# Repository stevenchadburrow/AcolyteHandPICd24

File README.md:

<b>Acolyte Hand PIC'd 24</b>

This is a single-chip retro-style computer using only the PIC24EP512GP204 microcontroller.  Inspired by Voja Antonic's design found here:  http://www.voja.rs/PROJECTS/GAME_HTM/1_intro.htm

It is designed to output VGA display at 320x240 with 16 colors, and 2-voice audio square waves.

It is designed to receive input from a Sega Genesis controller, PS/2 Keyboard or Mouse, and 8 on-board buttons.

It is designed to use a MicroSD Card Adapter, and an FT232RL USB Adapter.

Programmed using MPLAB IDE X via a PICkit3.

See my Youtube video for the Bad Apple demo. Either <a href="https://www.youtube.com/watch?v=rc4UsAqcSHg">without audio</a> or <a href="https://youtu.be/sSq6TWw3NXU">with audio</a>.

Also see my 'Pokemon Clone', video link <a href="https://youtu.be/8EHRpKk9gPc">here</a>.  Although I am using the Tuxemon game art assets, this project is not the Tuxemon game, nor are the creators of the Tuxemon game in charge of this project.  This project was simply inspired by the Tuxemon game.

Needed Changes:

*** LED silkscreen is confusing!!! ***

*** ICSP pins physically block the SDcard and FT232RL adapters!!! ***

*** Connected an MCP2221 to the USB connector for serial data transfer!!! ***

*** Tested with LCD, speaker, and with additional PIC24 chip for USB capability!!! ***

Updates:

Been working with the PIC24FJ128GB202 for USB capability.  Using the MLA projects from Microchip, I was able to combine USB Host capabilities for using Keyboad, Mouse, and Mass Storage Device.  See my .ZIP file for the entire project and all associated code.  It is connected to this main board through an RX/TX UART pair, currently at 9600 baud.  

A full 16-colors are available!

Tetra always seems to be the first game for any system.

It can even run Bad Apple!

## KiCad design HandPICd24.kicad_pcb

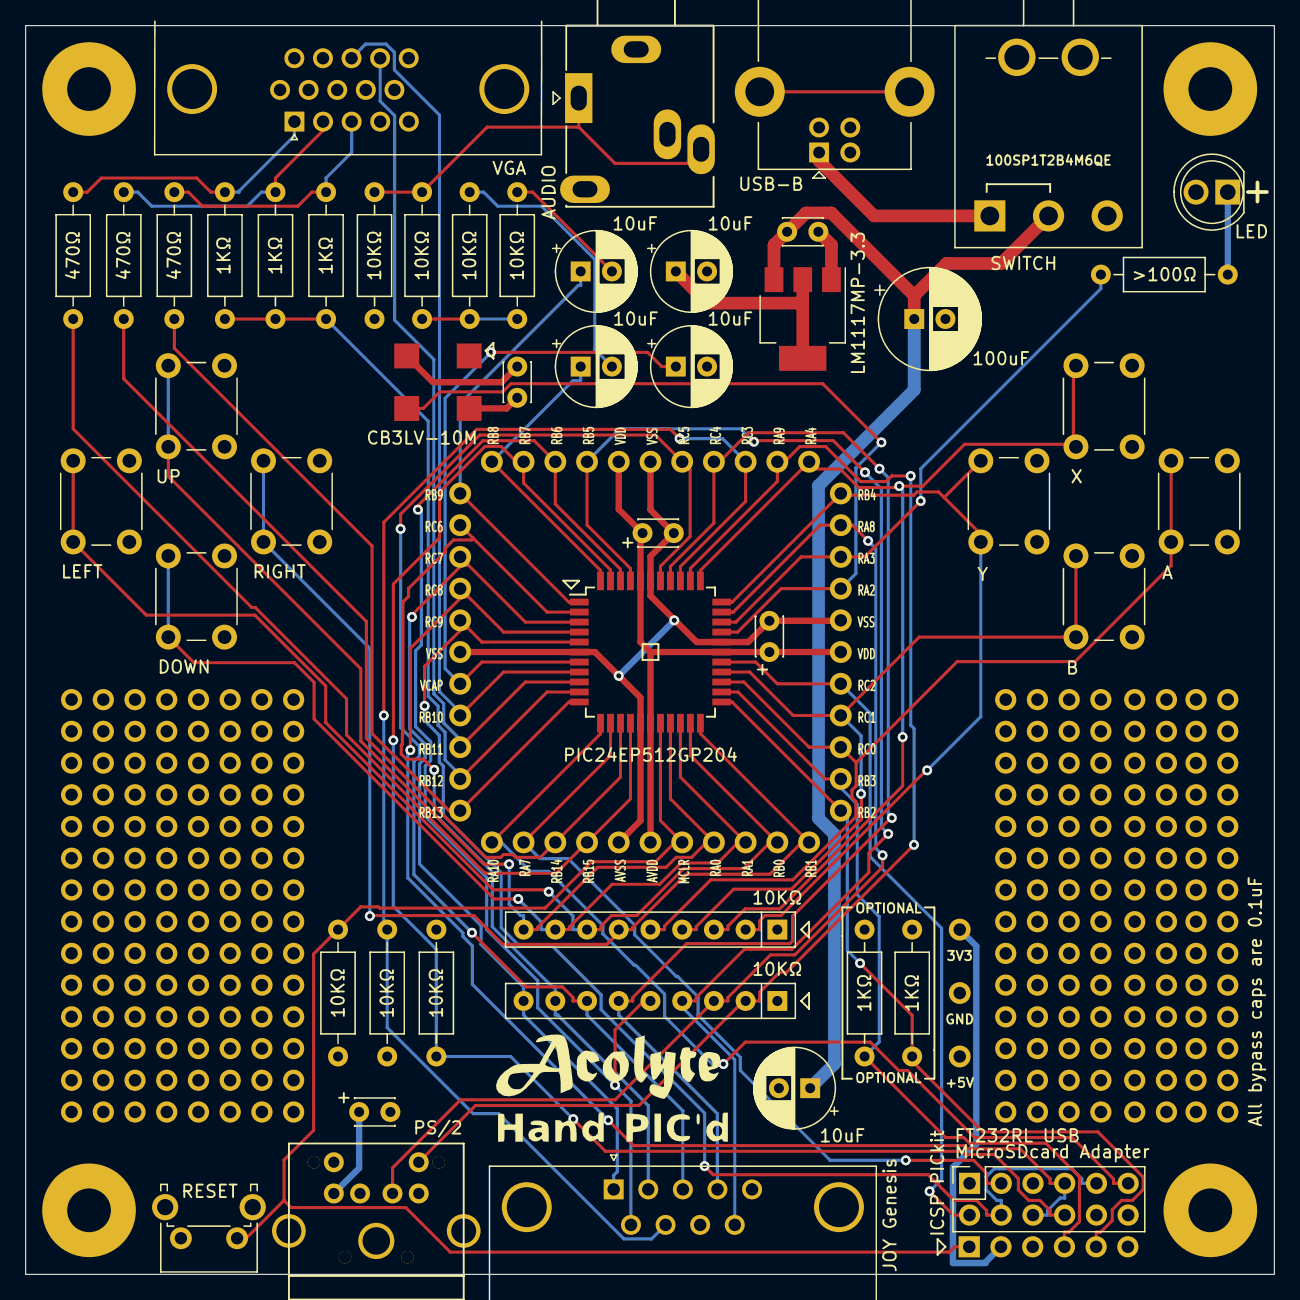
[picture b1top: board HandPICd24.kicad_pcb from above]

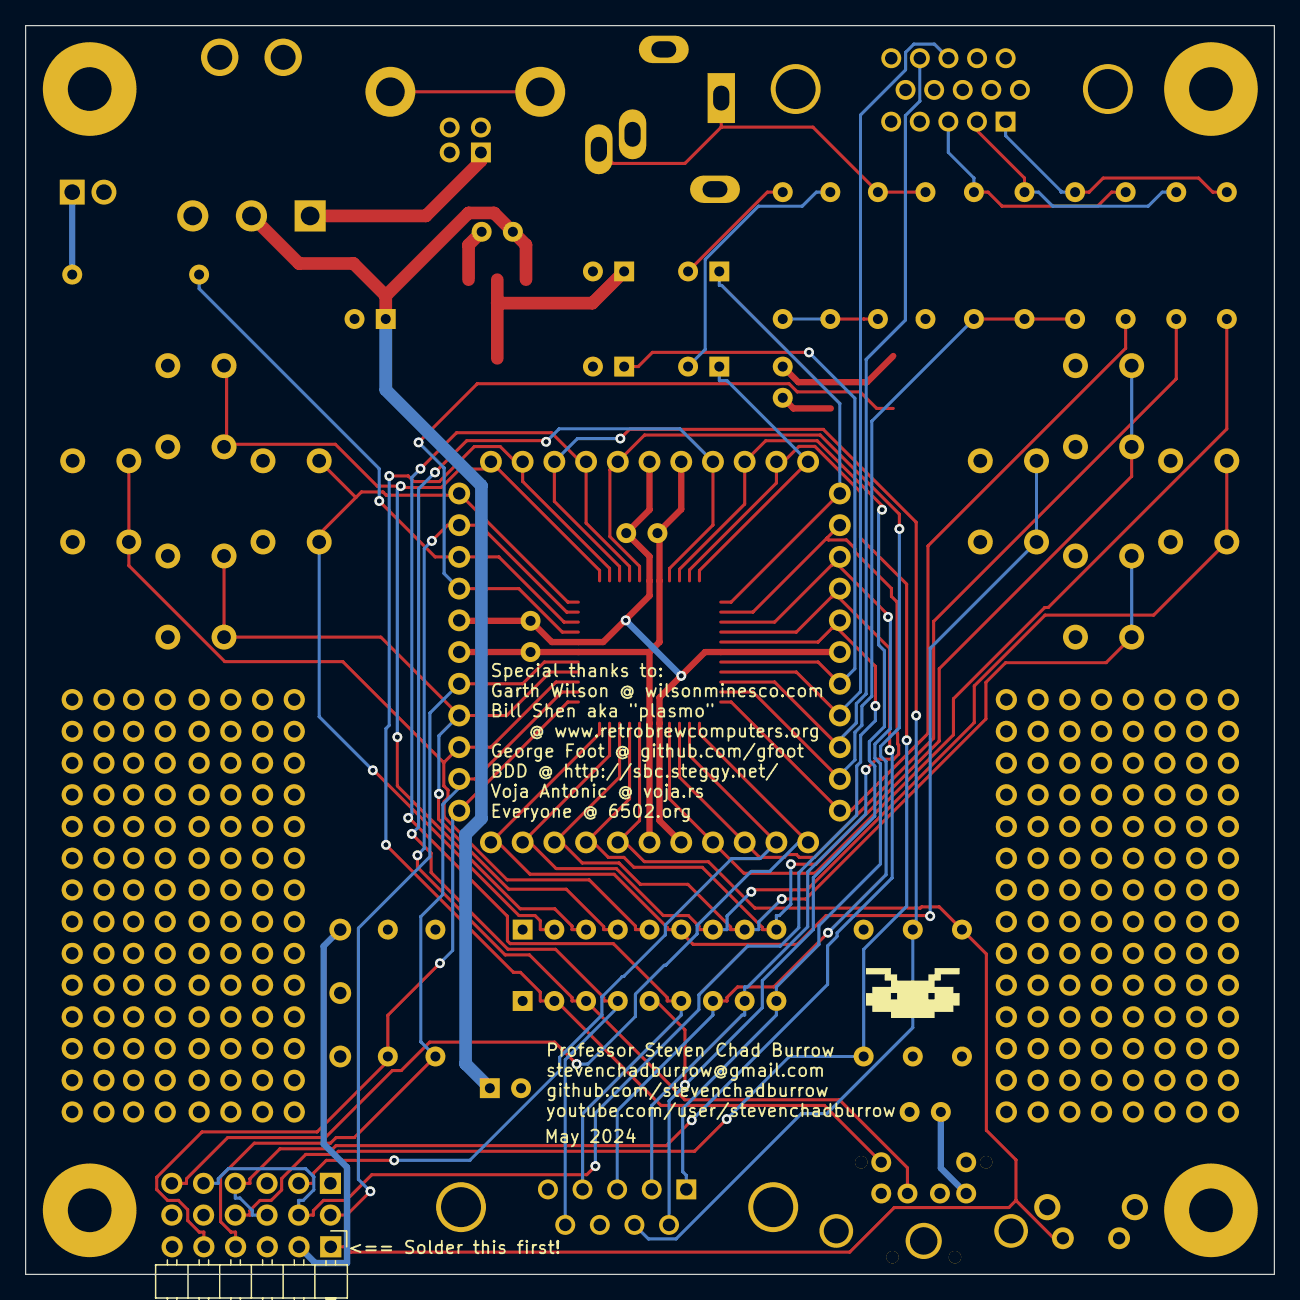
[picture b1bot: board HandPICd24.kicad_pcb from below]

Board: 4 copper layers, 100.0 x 100.0 mm, 112 parts (2 on the bottom side), 49 nets.

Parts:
C1, C3, C4, C6, C8: C_Polarized_Small_US; CP_Radial_D6.3mm_P2.50mm
C2: C_Polarized_US; CP_Radial_D8.0mm_P2.50mm
C5, C7, C19, C25, C28: C_Small; C_Disc_D3.0mm_W2.0mm_P2.50mm
D1: LED; CustomLED
G101: LOGO; AcolyteTitle
G102: LOGO; HandPickedTitle
G103: LOGO; Mystery
J1: Conn_02x06_Odd_Even; PinSocket_2x06_P2.54mm_Vertical
J2: Mini-DIN-6; PS2_Din6
J3: DE9_Plug; DSUB-9_Male_Horizontal_P2.77x2.84mm_EdgePinOffset7.70mm_Hou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
J4: USB_B; USB_B_Lumberg_2411_02_Horizontal
J5: DE15_Receptacle_HighDensity; DSUB-15-HD_Female_Horizontal_P2.29x2.54mm_VGA
J6: AudioJack3; BIGJack_3.5mm_Ledino_KB3SPRS_Horizontal
J10, J11, J12, J13, J14, J15, J16, J17: Conn_02x14_Odd_Even; BLANK-PinHeader_2x14_P2.54mm_Vertical
J18: Conn_01x06; PinHeader_1x06_P2.54mm_Horizontal
R1, R2, R3, R4, R5, R6, R7, R8, R9, R10, R11, R12, R13, R14, R15, R17: R_US; R_Axial_DIN0207_L6.3mm_D2.5mm_P10.16mm_Horizontal
RN1, RN2: R_Network08_US; R_Array_SIP9
SW1: SW_Push; SW_Tactile_SPST_Angled_PTS645Vx83-2LFS
SW2, SW4, SW5, SW6, SW7, SW8, SW9, SW10: SW_Push; SW_PUSH_6mm_H5mm
SW3: SW_SPDT; SPDT-100SP1T2B4M6QE
TP1, TP2, TP3, TP4: TestPoint; ScrewHole-4-40
TP5, TP6, TP7, TP8, TP9, TP10, TP11, TP12, TP13, TP14, TP15, TP16, TP17, TP18, TP19, TP20, TP21, TP22, TP23, TP24, TP25, TP26, TP27, TP28, TP29, TP30, TP31, TP32, TP33, TP34, TP35, TP36, TP37, TP38, TP39, TP40, TP41, TP42, TP43, TP44, TP45, TP46, TP47, TP48, TP49, TP50, TP53: TestPoint; TestPointStdTHT
U1: PIC24EP512GP204; TQFP-44_10x10mm_P0.8mm
U2: LM1117MP-3.3; SOT-223-3_TabPin2
X1: CB3LV; Oscillator_SMD_EuroQuartz_XO91-4Pin_7.0x5.0mm

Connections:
+3V3: C6.1, C19.2, C25.2, C28.2, D1.2 (A), J18.2, R4.2, R7.2, R15.2, RN2.1 (common), TP21.1, TP32.1, TP44.1, TP53.1, U1.17 (AVDD), U1.28 (VDD), U1.40 (VDD), U2.2 (VO), X1.4 (V+)
+5V: C2.1, C5.2, C7.2, C8.1, J1.10, J2.4, J3.5, R1.2, R17.2, RN1.1 (common), SW3.2 (B), TP50.1, U2.3 (VI)
AUDIO-COMBINED: R3.2, R5.1, R6.1
AUDIO-NEG-A: C4.2, R6.2
AUDIO-NEG-B: C3.2, R5.2
AUDIO-OUT: J6.R, J6.T, R2.2, R3.1
AUDIO-SOURCE-A: C4.1, TP5.1, U1.1 (RB9/RP41*+)
AUDIO-SOURCE-B: C3.1, TP48.1, U1.44 (RB8/RP40+)
BLUE: J5.3, R10.2, R13.2
BUTTON-A: RN2.5 (R4), SW7.1, TP29.1, U1.25 (RC0)
BUTTON-B: RN2.4 (R3), SW8.1, TP30.1, U1.26 (RC1)
BUTTON-DOWN: RN2.8 (R7), SW4.1, TP24.1, U1.20 (RA1)
BUTTON-LEFT: RN2.7 (R6), SW5.1, TP25.1, U1.21 (RB0/RPI32/PGED3)
BUTTON-RIGHT: RN2.6 (R5), SW6.1, TP26.1, U1.22 (RB1/RPI33/PGEC3)
BUTTON-UP: RN2.9 (R8), SW2.1, TP23.1, U1.19 (RA0)
BUTTON-X: RN2.3 (R2), SW9.1, TP38.1, U1.34 (RA4/RP20+)
BUTTON-Y: RN2.2 (R1), SW10.1, TP37.1, U1.33 (RB4/RP36*)
CTS: J1.3, TP17.1, U1.13 (RA7*)
DTR: J1.11, TP16.1, U1.12 (RA10*)
GND: C1.2, C2.2, C5.1, C6.2, C7.1, C8.2, C19.1, C25.1, C28.1, J1.1, J1.12, J2.3, J3.8, J4.4 (GND), J5.5, J5.6, J5.7, J5.8, J5.10, J6.S, J18.3, R2.1, SW1.2, SW2.2, SW4.2, SW5.2, SW6.2, SW7.2, SW8.2, SW9.2, SW10.2, TP1.1, TP2.1, TP3.1, TP4.1, TP10.1, TP20.1, TP33.1, TP43.1, TP49.1, U1.6 (VSS), U1.16 (AVSS), U1.29 (VSS), U1.39 (VSS), U2.1 (GND), X1.2 (GND)
GREEN: J5.2, R9.2, R12.2
H-SYNC: J5.13, TP12.1, U1.8 (RB10/RP42*+)
ICSP-CLK: J18.5, R4.1, TP27.1, U1.23 (RB2/RPI34/PGEC1)
ICSP-DAT: J18.4, R15.1, TP28.1, U1.24 (RB3/RP35/PGED1)
JOY-BUTTON1: J3.6, RN1.5 (R4), TP46.1, U1.42 (RB6/RP38/PGEC2*)
JOY-BUTTON2: J3.9, RN1.4 (R3), TP45.1, U1.41 (RB5/RP38/PGED2*)
JOY-DOWN: J3.2, RN1.8 (R7), TP6.1, U1.2 (RC6/RP54*)
JOY-LEFT: J3.3, RN1.7 (R6), TP42.1, U1.38 (RC5/RPI53*)
JOY-RIGHT: J3.4, RN1.6 (R5), TP41.1, U1.37 (RC4/RPI52*)
JOY-SELECT: J3.7, R17.1, TP40.1, U1.36 (RC3/RPI51*+)
JOY-UP: J3.1, RN1.9 (R8), TP7.1, U1.3 (RC7/RP55*)
LED: R14.2, TP35.1, U1.31 (RA3/CLKO+)
LED-MID: D1.1 (K), R14.1
MCLK: TP34.1, U1.30 (RA2/CLKI), X1.3 (OUT)
PIX-BLUE: R10.1, TP15.1, U1.11 (RB13/RPI45*+)
PIX-GREEN: R9.1, TP18.1, U1.14 (RB14/RPI46*+)
PIX-INTENSITY: R11.1, R12.1, R13.1, TP14.1, U1.10 (RB12/RBI44*+)
PIX-RED: R8.1, TP19.1, U1.15 (RB15/RPI47*+)
POWER-INPUT: J4.1 (VBUS), SW3.1 (A)
PS2-CLK: J2.5, RN1.2 (R1), TP39.1, U1.35 (RA9/RPI25*+)
PS2-DAT: J2.1, RN1.3 (R2), TP36.1, U1.32 (RA8/RPI24*)
RED: J5.1, R8.2, R11.2
SPI-CLK/TX: J1.4, J1.9, TP9.1, U1.5 (RC9/RP57*)
SPI-CS: J1.2, TP31.1, U1.27 (RC2)
SPI-MISO/INT: J1.8, R7.1, TP47.1, U1.43 (RB7/RP39/INT0+)
SPI-MOSI/RX: J1.6, J1.7, TP8.1, U1.4 (RC8/RP56*)
V-SYNC: J5.14, TP13.1, U1.9 (RB11/RP43*+)
VCAP: C1.1, TP11.1, U1.7 (VCAP)
~MCLR: J18.1, R1.1, SW1.1, TP22.1, U1.18 (~MCLR*)

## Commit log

2024-08-24 Create LICENSE
